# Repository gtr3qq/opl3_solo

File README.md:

# OPL3 SOLO!
A Arduino(TM) and all Single-Chip Microcontroler usable FM Synth. Driven by genuine ymf262/yac512
_______________________________________________________________________________
# This portject is under construction,untested.Though should work.
-------------------------------------------------------------------------------

This is some little pet project I've been cooking,a easy to use ,has limited software library,cost effective FM Syth.  
_________________________________________________
Introducing OPL3 SOLO!

Digital side is designed to be Pin/Register compactible with OPL2 Audio Board (A Tradmark of Cheerful Electronic.NL).25% compactible with OPL3 Duo!(A Tradmark of Cheerful Electronic.NL) by minor tweaks of code.
https://www.tindie.com/products/cheerful/opl2-audio-board/
https://www.tindie.com/products/cheerful/opl3-duo/
S.W.Lib. :https://github.com/DhrBaksteen/ArduinoOPL2

The Anlog side is Based on Texelec's Resound OPL v1.1 board's output:
https://www.tindie.com/products/TexElec/resound-opl3-4-channel-sound-card-8-bit-isa/

Pictures
------------

The capacitors do double-duty as stand-offs.

Disclaimer
-----------
It is built out of pure intrest,with intendtion to share ideas and proof it work.
Not use it for profit.
I high recommanded you to cheek out mentioned repositorys to suport them if possible.

--------
--------
--------
--------
--------
--------
--------
--------
--------
--------
--------
please don't sue me.
--------

License
------------
<br />This work is licensed under a <a rel="license" href="http://creativecommons.org/licenses/by-sa/4.0/">Creative Commons Attribution-ShareAlike 4.0 International License</a>.

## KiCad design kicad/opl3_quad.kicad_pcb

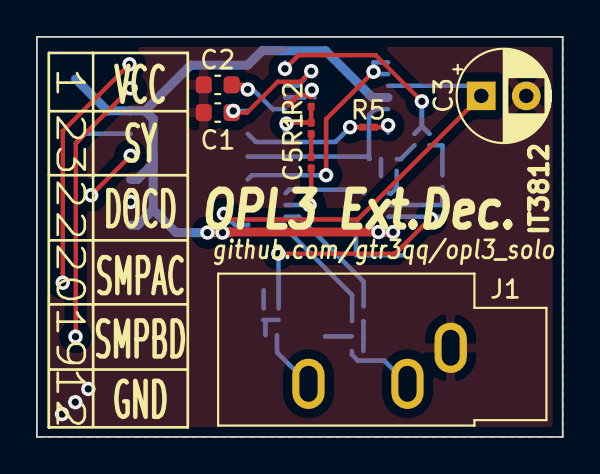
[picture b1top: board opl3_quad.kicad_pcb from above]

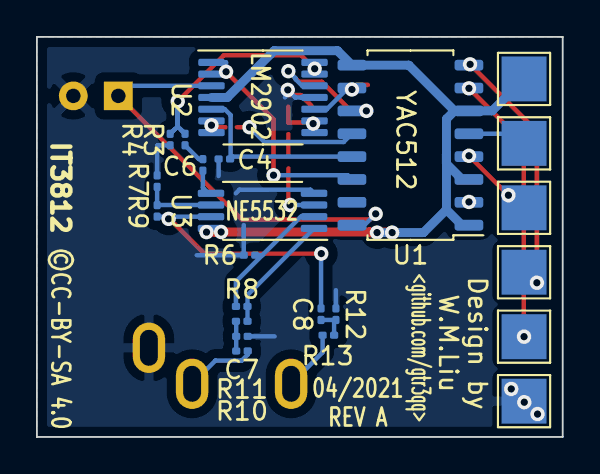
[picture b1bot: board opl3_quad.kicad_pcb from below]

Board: 2 copper layers, 29.2 x 22.2 mm, 26 parts (18 on the bottom side), 27 nets.

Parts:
C1, C2: 2.7nF; C_0603_1608Metric
C3: 10uF; CP_Radial_D5.0mm_P2.50mm
C4: 68pF; C_0201_0603Metric
C5, C6, C7, C8: 1uF; C_0201_0603Metric
J1: AudioJack2_Ground_Switch; Jack_3.5mm_CUI_SJ1-3533NG_Horizontal
J2: Conn_01x06; TestPoint_Pad_2.5x2.5mm_x5
R1, R3, R6, R7, R8, R9, R11, R12: 10K; R_0201_0603Metric
R2, R4: 100K; R_0201_0603Metric
R5: 33; R_0201_0603Metric
R10, R13: 330; R_0201_0603Metric
U1: YAC512; SOP-16_4.55x10.3mm_P1.27mm
U2: LM2902; TSSOP-14_4.4x5mm_P0.65mm
U3: NE5532; TSSOP-8_4.4x3mm_P0.65mm

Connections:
+5V: J2.1, U1.1, U1.3, U1.6, U1.9, U2.4, U3.8
/DOCD: J2.3, U1.4
/SMPAC: J2.4, U1.8
/SMPBD: J2.5, U1.7
/SY: J2.2, U1.5
GND: C1.2, C2.1, C3.2, C4.1, J1.S, J2.6, R2.2, R4.1, R6.2, R7.2, R11.1, R12.1, U1.2, U2.11, U3.4
unnamed: C1.1, U1.11, U2.12
unnamed: C2.2, U1.10, U2.10
unnamed: C3.1, U1.16, U2.3
unnamed: C4.2, U1.13, U2.5
unnamed: C5.1, U3.3
unnamed: C5.2, R1.1
unnamed: C6.1, U3.5
unnamed: C6.2, R3.1
unnamed: C7.1, R10.2, R11.2
unnamed: C7.2, R8.1, U3.1
unnamed: C8.1, R12.2, R13.2
unnamed: C8.2, R9.1, U3.7
unnamed: J1.R, R13.1
unnamed: J1.T, R10.1
unnamed: R1.2, R2.1, U2.8, U2.9
unnamed: R3.2, R4.2, U2.13, U2.14
unnamed: R5.1, U2.6, U2.7
unnamed: R5.2, U1.12
unnamed: R6.1, R8.2, U3.2
unnamed: R7.1, R9.2, U3.6
unnamed: U1.14, U2.1, U2.2

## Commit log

2021-01-14 Create LICENSE
2021-01-17 A add on module enables ALL opl3's channel.
2021-01-17 more pic.

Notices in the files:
kicad/opl3_quad.kicad_pcb:
©CC-BY-SA 4.0
